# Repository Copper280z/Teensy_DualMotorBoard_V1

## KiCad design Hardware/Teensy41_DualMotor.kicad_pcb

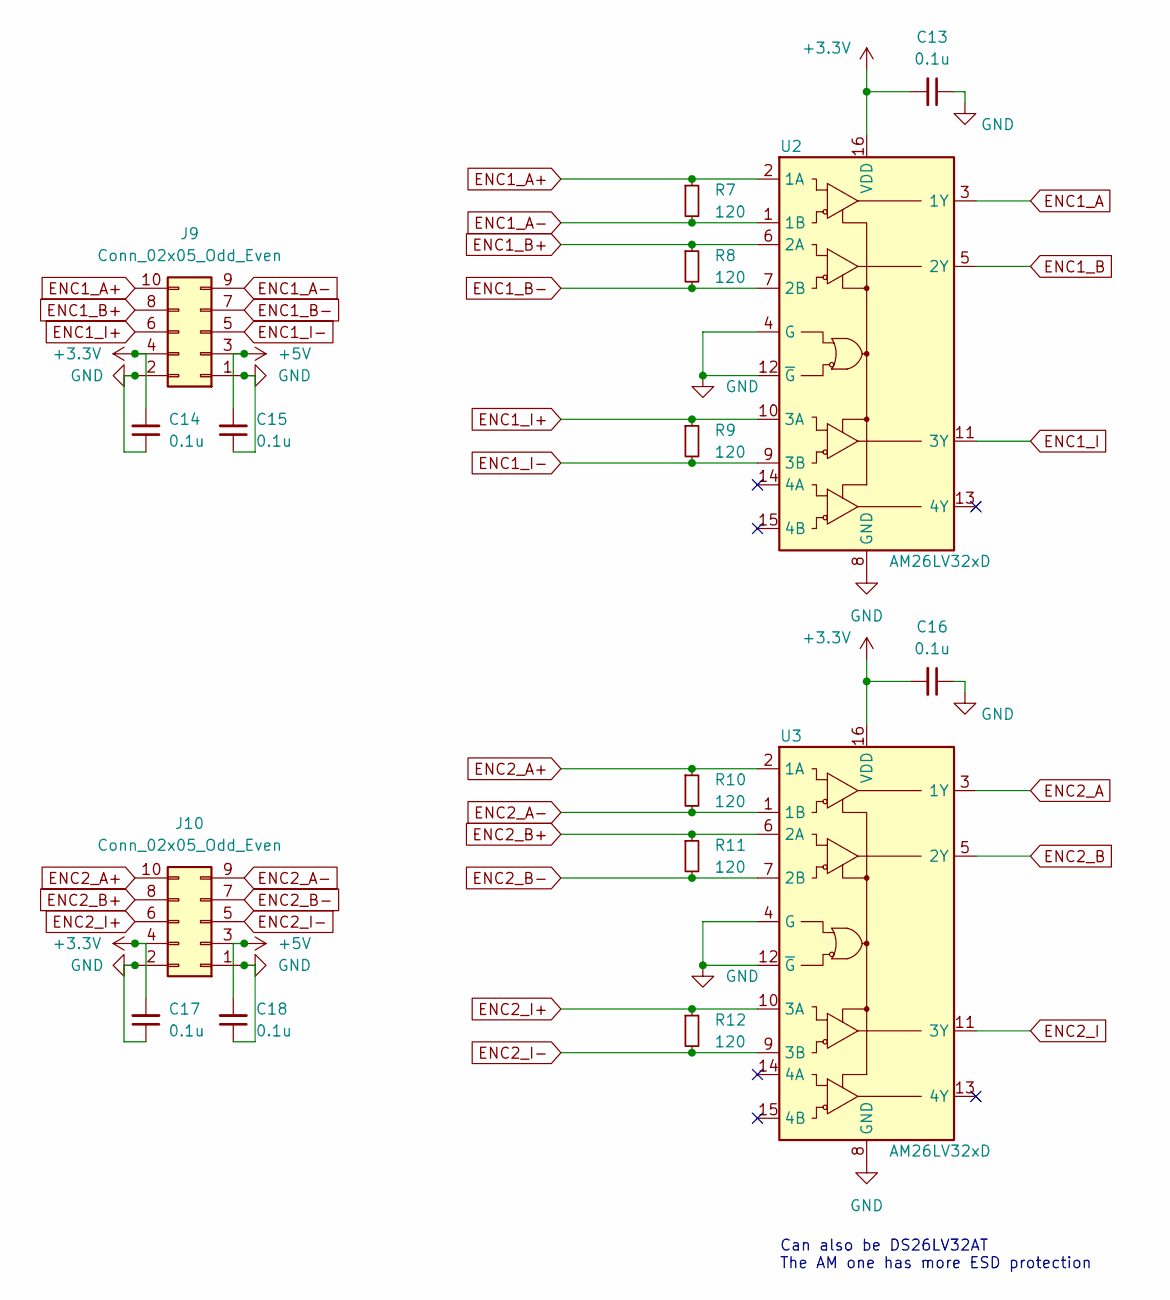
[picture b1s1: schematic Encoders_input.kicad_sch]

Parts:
C13, C14, C15, C16, C17, C18: 0.1u; C_0603_1608Metric_Pad1.08x0.95mm_HandSolder
J9, J10: Conn_02x05_Odd_Even; PinSocket_2x05_P2.54mm_Vertical
R7, R8, R9, R10, R11, R12: 120; R_0603_1608Metric_Pad0.98x0.95mm_HandSolder
U2, U3: AM26LV32xD; SOIC-16_3.9x9.9mm_P1.27mm

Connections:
+3V3: C13.2, C14.2, C16.2, C17.2, J9.4, J10.4, U2.16 (VDD), U3.16 (VDD); also elsewhere on the board
+5V: C15.2, C18.2, J9.3, J10.3; also elsewhere on the board
ENC1_A: U2.3 (1Y); also elsewhere on the board
ENC1_A+: J9.10, R7.1, U2.2 (1A)
ENC1_A-: J9.9, R7.2, U2.1 (1B)
ENC1_B: U2.5 (2Y); also elsewhere on the board
ENC1_B+: J9.8, R8.1, U2.6 (2A)
ENC1_B-: J9.7, R8.2, U2.7 (2B)
ENC1_I: U2.11 (3Y); also elsewhere on the board
ENC1_I+: J9.6, R9.1, U2.10 (3A)
ENC1_I-: J9.5, R9.2, U2.9 (3B)
ENC2_A: U3.3 (1Y); also elsewhere on the board
ENC2_A+: J10.10, R10.1, U3.2 (1A)
ENC2_A-: J10.9, R10.2, U3.1 (1B)
ENC2_B: U3.5 (2Y); also elsewhere on the board
ENC2_B+: J10.8, R11.1, U3.6 (2A)
ENC2_B-: J10.7, R11.2, U3.7 (2B)
ENC2_I: U3.11 (3Y); also elsewhere on the board
ENC2_I+: J10.6, R12.1, U3.10 (3A)
ENC2_I-: J10.5, R12.2, U3.9 (3B)
GND: C13.1, C14.1, C15.1, C16.1, C17.1, C18.1, J9.1, J9.2, J10.1, J10.2, U2.4 (G), U2.8 (GND), U2.12 (~G), U3.4 (G), U3.8 (GND), U3.12 (~G); also elsewhere on the board

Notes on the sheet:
Can also be DS26LV32AT The AM one has more ESD protection

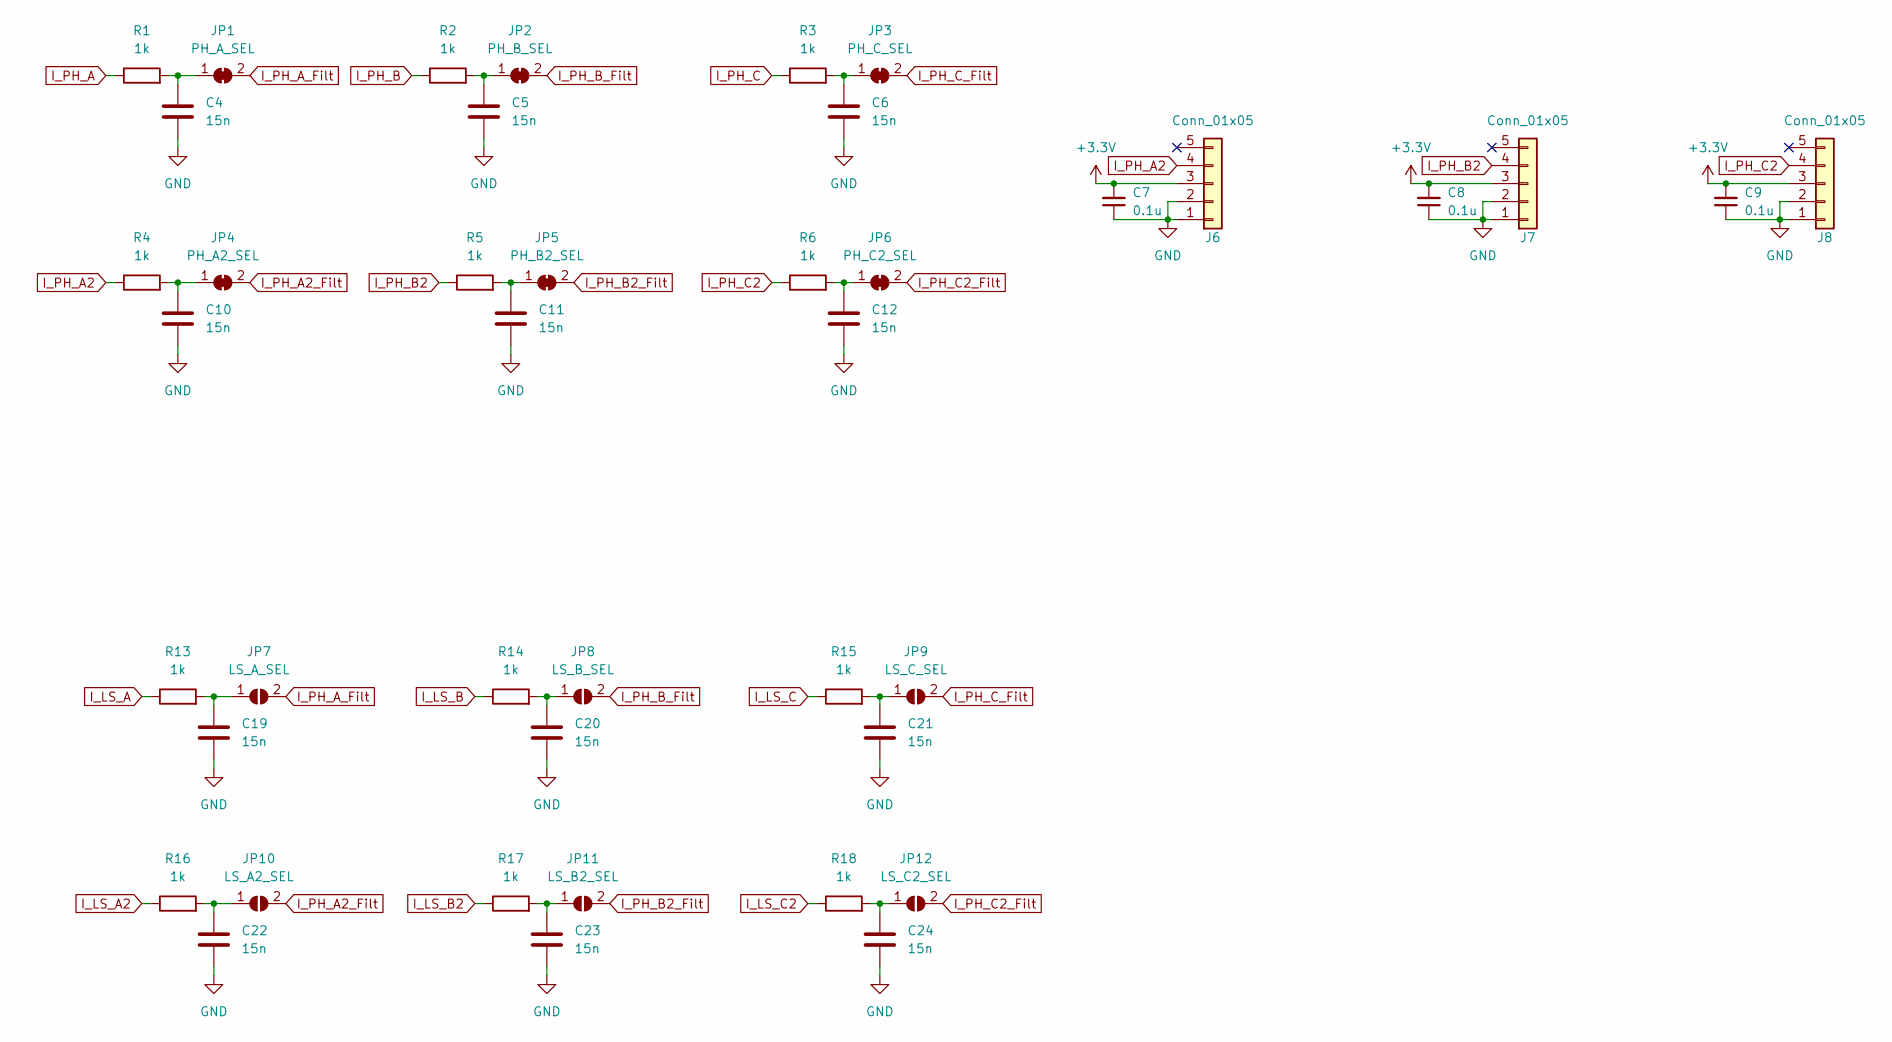
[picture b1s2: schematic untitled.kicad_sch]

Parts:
C4, C5, C6, C10, C11, C12, C19, C20, C21, C22, C23, C24: 15n; C_0603_1608Metric_Pad1.08x0.95mm_HandSolder
C7, C8, C9: 0.1u; C_0603_1608Metric_Pad1.08x0.95mm_HandSolder
J6, J7, J8: Conn_01x05; PinSocket_1x05_P2.54mm_Vertical
JP1: PH_A_SEL; SolderJumper-2_P1.3mm_Bridged_RoundedPad1.0x1.5mm
JP2: PH_B_SEL; SolderJumper-2_P1.3mm_Bridged_RoundedPad1.0x1.5mm
JP3: PH_C_SEL; SolderJumper-2_P1.3mm_Bridged_RoundedPad1.0x1.5mm
JP4: PH_A2_SEL; SolderJumper-2_P1.3mm_Bridged_RoundedPad1.0x1.5mm
JP5: PH_B2_SEL; SolderJumper-2_P1.3mm_Bridged_RoundedPad1.0x1.5mm
JP6: PH_C2_SEL; SolderJumper-2_P1.3mm_Bridged_RoundedPad1.0x1.5mm
JP7: LS_A_SEL; SolderJumper-2_P1.3mm_Open_RoundedPad1.0x1.5mm
JP8: LS_B_SEL; SolderJumper-2_P1.3mm_Open_RoundedPad1.0x1.5mm
JP9: LS_C_SEL; SolderJumper-2_P1.3mm_Open_RoundedPad1.0x1.5mm
JP10: LS_A2_SEL; SolderJumper-2_P1.3mm_Open_RoundedPad1.0x1.5mm
JP11: LS_B2_SEL; SolderJumper-2_P1.3mm_Open_RoundedPad1.0x1.5mm
JP12: LS_C2_SEL; SolderJumper-2_P1.3mm_Open_RoundedPad1.0x1.5mm
R1, R2, R3, R4, R5, R6, R13, R14, R15, R16, R17, R18: 1k; R_0603_1608Metric_Pad0.98x0.95mm_HandSolder

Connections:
+3V3: C7.2, C8.2, C9.2, J6.3, J7.3, J8.3; also elsewhere on the board
GND: C4.2, C5.2, C6.2, C7.1, C8.1, C9.1, C10.2, C11.2, C12.2, C19.2, C20.2, C21.2, C22.2, C23.2, C24.2, J6.1, J6.2, J7.1, J7.2, J8.1, J8.2; also elsewhere on the board
I_LS_A: R13.1; also elsewhere on the board
I_LS_A2: R16.1; also elsewhere on the board
I_LS_B: R14.1; also elsewhere on the board
I_LS_B2: R17.1; also elsewhere on the board
I_LS_C: R15.1; also elsewhere on the board
I_LS_C2: R18.1; also elsewhere on the board
I_PH_A: R1.1; also elsewhere on the board
I_PH_A2: J6.4, R4.1
I_PH_A2_Filt: JP4.2 (B), JP10.2 (B); also elsewhere on the board
I_PH_A_Filt: JP1.2 (B), JP7.2 (B); also elsewhere on the board
I_PH_B: R2.1; also elsewhere on the board
I_PH_B2: J7.4, R5.1
I_PH_B2_Filt: JP5.2 (B), JP11.2 (B); also elsewhere on the board
I_PH_B_Filt: JP2.2 (B), JP8.2 (B); also elsewhere on the board
I_PH_C: R3.1; also elsewhere on the board
I_PH_C2: J8.4, R6.1
I_PH_C2_Filt: JP6.2 (B), JP12.2 (B); also elsewhere on the board
I_PH_C_Filt: JP3.2 (B), JP9.2 (B); also elsewhere on the board
unnamed: C4.1, JP1.1 (A), R1.2
unnamed: C5.1, JP2.1 (A), R2.2
unnamed: C6.1, JP3.1 (A), R3.2
unnamed: C10.1, JP4.1 (A), R4.2
unnamed: C11.1, JP5.1 (A), R5.2
unnamed: C12.1, JP6.1 (A), R6.2
unnamed: C19.1, JP7.1 (A), R13.2
unnamed: C20.1, JP8.1 (A), R14.2
unnamed: C21.1, JP9.1 (A), R15.2
unnamed: C22.1, JP10.1 (A), R16.2
unnamed: C23.1, JP11.1 (A), R17.2
unnamed: C24.1, JP12.1 (A), R18.2

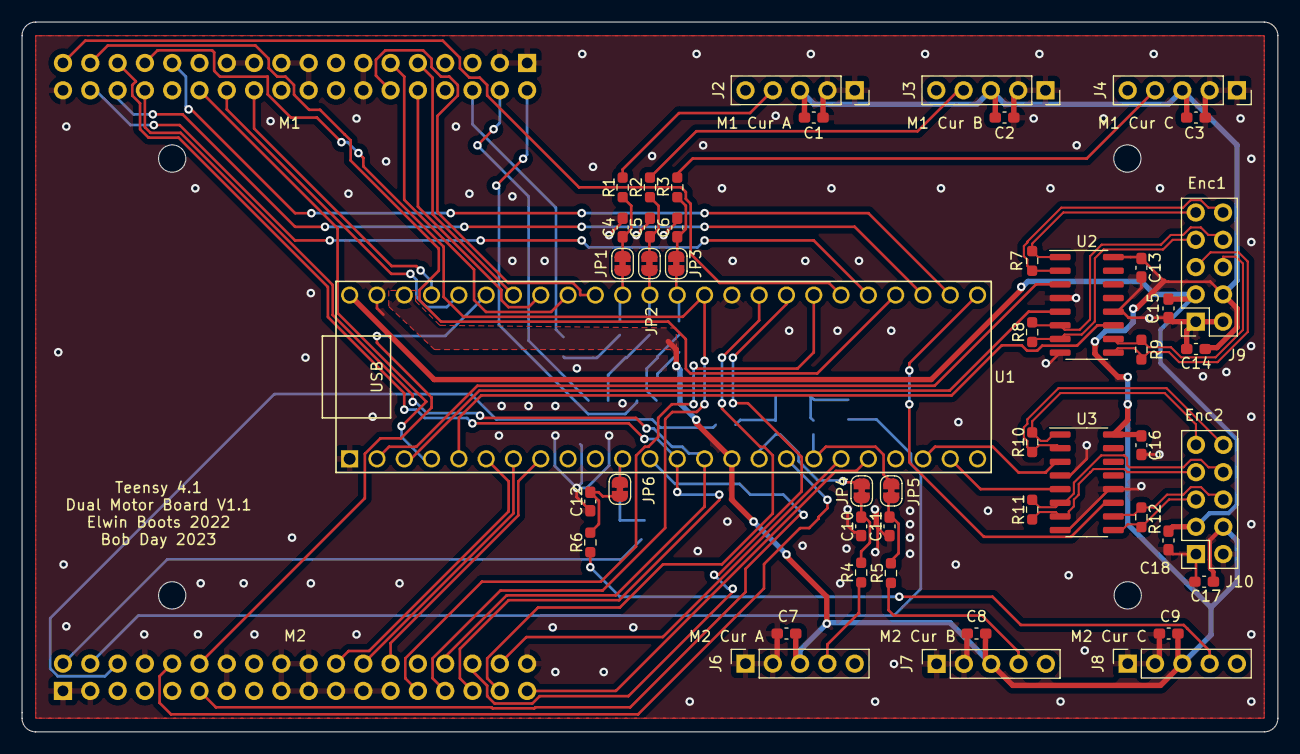
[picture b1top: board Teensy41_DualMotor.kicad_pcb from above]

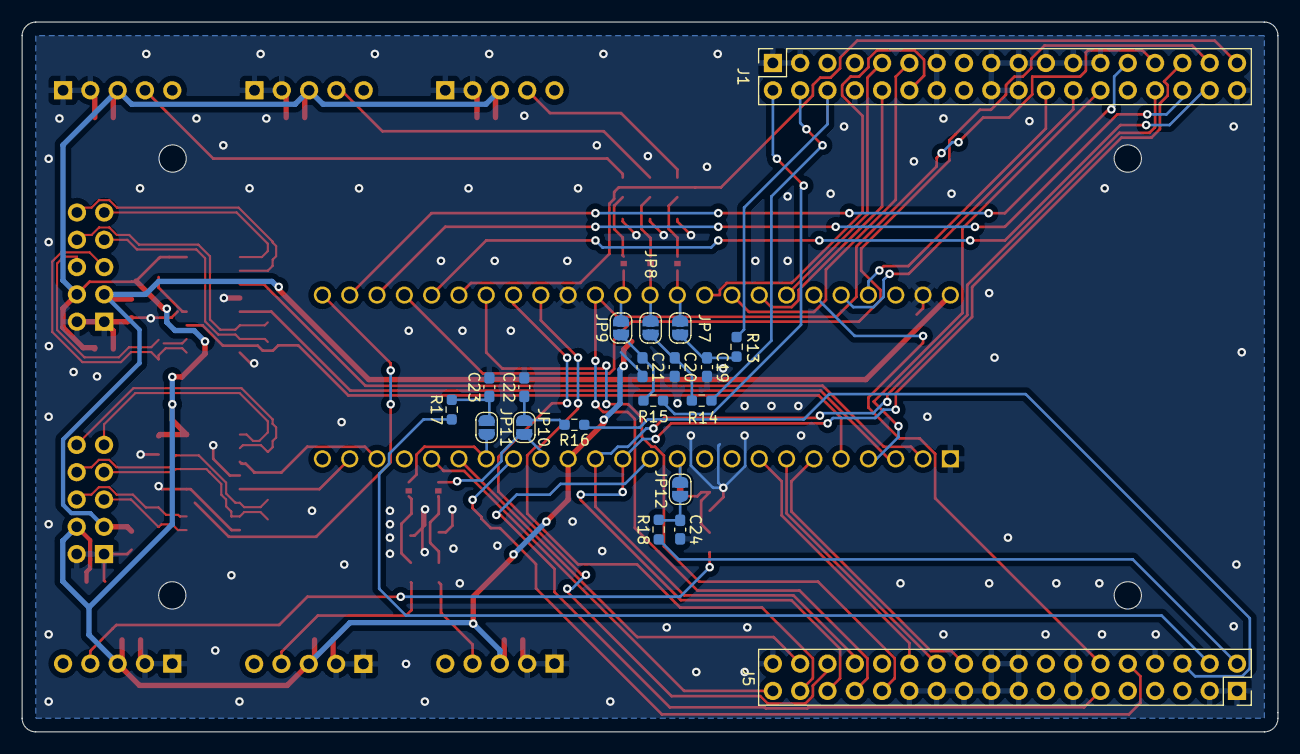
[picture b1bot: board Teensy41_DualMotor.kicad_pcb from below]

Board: 2 copper layers, 116.8 x 66.0 mm, 67 parts (20 on the bottom side), 77 nets.

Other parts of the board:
C1, C2, C3: 0.1u; C_0603_1608Metric_Pad1.08x0.95mm_HandSolder
J1, J5: Conn_02x18_Odd_Even; PinSocket_2x18_P2.54mm_Vertical
J2, J3, J4: Conn_01x05; PinSocket_1x05_P2.54mm_Vertical
U1: Teensy4.1; Teensy41

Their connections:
+3V3: C1.2, C2.2, C3.2, J2.3, J3.3, J4.3, U1.15 (3V3), U1.46 (3V3); also elsewhere on the board
+5V: U1.48 (VIN); also elsewhere on the board
EMF-A: J1.11, U1.40 (18_A4_SDA)
EMF-A2: J5.11, U1.12 (10_CS_MQSR)
EMF-B: J1.10, U1.41 (19_A5_SCL)
EMF-B2: J5.10, U1.17 (25_A11_RX6_SDA2)
EMF-C: J1.9, U1.42 (20_A6_TX5_LRCLK1)
EN-GATE: J1.27, U1.26 (34_RX8)
EN-GATE2: J5.27, U1.31 (39_MISO1_OUT1A)
ENC1_A: U1.2 (0_RX1_CRX2_CS1); also elsewhere on the board
ENC1_B: U1.3 (1_TX1_CTX2_MISO1); also elsewhere on the board
ENC1_I: U1.5 (3_LRCLK2); also elsewhere on the board
ENC2_A: U1.22 (30_CRX3); also elsewhere on the board
ENC2_B: U1.23 (31_CTX3); also elsewhere on the board
ENC2_I: U1.25 (33_MCLK2); also elsewhere on the board
GND: C1.1, C2.1, C3.1, J1.1, J1.3, J1.8, J1.13, J1.14, J1.17, J1.18, J1.19, J1.20, J1.21, J1.23, J1.25, J1.36, J2.1, J2.2, J3.1, J3.2, J4.1, J4.2, J5.1, J5.3, J5.8, J5.13, J5.14, J5.17, J5.18, J5.19, J5.20, J5.21, J5.23, J5.25, J5.36, U1.1 (GND), U1.34 (GND), U1.47 (GND); also elsewhere on the board
INH-A: J1.26, U1.4 (2_OUT2)
INH-A2: J5.26, U1.8 (6_OUT1D)
INH-B: J1.24, U1.44 (22_A8_CTX1)
INH-B2: J5.24, U1.7 (5_IN2)
INH-C: J1.22, U1.45 (23_A9_CRX1_MCLK1)
INH-C2: J5.22, U1.6 (4_BCLK2)
I_LS_A: J1.6; also elsewhere on the board
I_LS_A2: J5.6; also elsewhere on the board
I_LS_B: J1.4; also elsewhere on the board
I_LS_B2: J5.4; also elsewhere on the board
I_LS_C: J1.2; also elsewhere on the board
I_LS_C2: J5.2; also elsewhere on the board
I_PH_A: J2.4; also elsewhere on the board
I_PH_A2_Filt: U1.16 (24_A10_TX6_SCL2); also elsewhere on the board
I_PH_A_Filt: U1.38 (16_A2_RX4_SCL1); also elsewhere on the board
I_PH_B: J3.4; also elsewhere on the board
I_PH_B2_Filt: U1.18 (26_A12_MOSI1); also elsewhere on the board
I_PH_B_Filt: U1.37 (15_A1_RX3_SPDIF_IN); also elsewhere on the board
I_PH_C: J4.4; also elsewhere on the board
I_PH_C2_Filt: U1.11 (9_OUT1C); also elsewhere on the board
I_PH_C_Filt: U1.36 (14_A0_TX3_SPDIF_OUT); also elsewhere on the board
PWRGD: J1.35, U1.30 (38_CS1_IN1)
PWRGD2: J5.35, U1.20 (28_RX7)
SCLK: J1.29, J5.29, U1.35 (13_SCK_LED)
SDI: J1.31, J5.31, U1.13 (11_MOSI_CTX1)
SDO: J1.30, J5.30, U1.14 (12_MISO_MQSL)
VPDD-O: J1.12, U1.39 (17_A3_TX4_SDA1)
VPDD-O2: J5.12, U1.43 (21_A7_RX5_BCLK1)
nFAULT: J1.33, U1.28 (36_CS)
nFAULT2: J5.33, U1.33 (41_A17)
nOCTW: J1.34, U1.29 (37_CS)
nOCTW2: J5.34, U1.19 (27_A13_SCK1)
nSCS: J1.32, U1.27 (35_TX8)
nSCS2: J5.32, U1.32 (40_A16)

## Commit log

2024-01-06 added filters and solder bridges to select low side current sense or external inline current sense
2024-01-16 added some macros to firmware for LS vs inline current sense
2024-01-22 working hfi with 2805 gimbal motor
2024-01-24 works well with 2805 motor
2024-01-24 added hfi mode 6 which uses a linear fit coefficients to calculate L given I
2024-01-25 changed setpoint stuff
2024-01-25 generated trace file for inductance lookup, turned up accel and jerk more for setpoint moves
2024-02-23 add script for characterizing motors
2024-02-27 firmware updates
2024-02-27 added 4215 motor file and anticog calibration script
2024-02-27 minor update for motor characterization
2024-02-27 added anticogging to firmware
2024-04-26 anticogging implementation
2024-12-08 remove some filtering in anticog impl, add measuring in both directions
2024-12-08 update anitcog script
2024-12-09 bug fixes and revisions, add iterative building of cogging map
2024-12-09 change a constant
